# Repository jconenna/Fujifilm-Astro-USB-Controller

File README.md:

# Fujifilm-Astro-USB-Controller

USB Serial shutter release device for Fujifilm cameras, geared towards **Astrophotography** use.

## Description

This device was made in response to a lack of tethering options for Fujifilm cameras for **Astrophotography control**, though it can be used for general shutter release needs with manual lenses or lenses with autofocus disabled.</br>

This device allows a compatible Fujifilm camera to be controlled by [digiCamControl](http://digicamcontrol.com/) software (free, MS Windows) with its "Astro" intervalometer mode, which interoperates with [PHD2](https://openphdguiding.org/) software, allowing for autoguiding a mount and dithering between frames.</br>

The device was made using common, inexpensive, and easy to assemble parts that can be sourced from places like Amazon, Ebay, Sparkfun, and other retailers.</br>

An optoisolator isolates the 5V computer side circuit from the shutter release camera side of the circuit, providing some added safety.</br>

This has been tested working with an X-T100 and X-S10, and should work with other similarly controlled Fujifilm cameras (e.g. X-T#, X-T##, X-E#, X-T###, X###C, etc.) If you try this and it works for your camera let me know so I can build a compatibility list.</br>

This device has been tested working with some Canon cameras that use the 3 pin shutter release, though I am marketing this for Fujifilm folks since there is no BackyardFuji or other tethering option for most cameras.</br>

For astrophotography use with digiCamControl software, it has been tested working with an X-T100, camera lens, and Star Adventurer mount guided with PHD2 using an ASI120MM-Mini guide cam and 30mm guide scope, dithering between frames.</br>

You **may** be able to use this device with other camera control software that has a "Serial Shutter Release" option that uses the RTS signal as the signal to the device. </br>

## Theory of Operation
This device works by using software on a computer to control the RTS signal of an RS-232 connection (USB to Serial Converter in this case). The RTS signal from the Converter used here is inverted using a transistor since it comes from the FTDI chip inverted (cannot change EEPROM setting of **this** converter). When the signal reaching the optoisolator is asserted it turns on the internal IR LED whose photons turn on the internal IR Photodiode on the shutter release side, connecting the Shutter/Focus pins to the Ground pin of the shutter release cable, thereby closing the camera shutter.</br>

From inspection of commercial shutter release products for Fujifilm cameras, it was found that a successful shutter release depends on activating the focus pin before the shutter pin. For astrophotography a telescope or manually focused lens is typically used, thus the focus activation has no ill effect on composition. This device simultaneously activates the focus and shutter pins, successfully closing the shutter on the camera.</br> 

## What's Included
Included are the Eagle PCB files for ordering a board. Boards can be easily [purchased from OSH Park](https://oshpark.com/shared_projects/9drAsv7N) for around $11 for 3 boards. If you choose to order elsewhere, the 3D files are designed for a PCB thickness of 1.5-1.6mm. Note: I have no affiliation with OSH Park, but love their services.

Included are two stl files for 3D printing a case. This contains a top and bottom piece that snap together and can be easily printed without supports by a wide variety of printers. I used PLA material with default print settings on an Ender 3 Pro printer. 

## Bill of Materials:
1 - FT232RL USB to TTL Serial Converter module (red PCB with Mini USB female connector)<br/>
1 - PJ-307 3.5 mm Audio Jack Connector PCB Mount Female Socket 5 Pin<br/>
1 - 4N25 Optoisolator (6 pin DIP, white)<br/>
1 - 2N2222 NPN Transistor (TO-92 package)<br/>
2 - 1 kOhm Axial Resistor (common through hole resistor)<br/>
1 - 50 Ohm Axial Resistor (common through hole resistor)<br/>

## In addition you will need:
1 - A-Male to Mini-B USB Cable, length of your choice<br/>
1 - 3.5mm Audio Cable, length of your choice<br/>
1 - 3.5mm Female to 2.5mm Male adapter, preferably the short cable type with right angle 2.5mm connector<br/>
OR instead of the 2 previous items 1 - 3.5mm male to 2.5mm male Audio cable<br/>

## Tutorial

#### Assembly

[Here is a video showing from start to finish how I solder the components to the board.](https://youtu.be/rFp3plmKMuA)

#### Use with digiCamControl

1. [Download FTDI drivers here](https://cdn.sparkfun.com/assets/learn_tutorials/7/4/CDM21228_Setup.exe), or visit [FTDI's VCP Drivers page](https://ftdichip.com/drivers/) for the latest download of the Windows FTDI Driver executable.
2. Install the drivers using the executable file.
3. Open Windows Device Manager (Win-R, devmgmt.msc, OK).
4. Plug in the Fujifilm-Astro-USB-Controller device using the USB Mini cable.
5. Click the drop-down arrow for **Ports** and note "USB Serial Port" device. Right-click, properties, and note Manufacturer: FTDI. 
6. Note the COM number assigned to the device, in this case COM7.</br>

7. Download the latest stable version of [digiCamControl](http://digicamcontrol.com/download) and install.
8. Open digiCamControl.
9. Go to File > Settings.
10. In the popup window click on Devices, under available devices click Add.
11. Name the device under Configuration, set the driver as **Serial Port Shutter Release**, and Com Port to the COM port of the device.</br>

12. Click Ok in the bottom left of the Settings window to exit.
13. On the top toolbar click on the Astronomy button.</br>

14. In the popup BULB window, under the **External shutter release** menu, select enable and chose the device you just set up.</br>

15. Set the imaging session parameters:</br>

16. Set **Capture time** value in seconds.
17. Set **Number of photos** to set how many frames to capture before stopping.
18. Set **Time between shots** value in seconds. For non guided imaging I usually set this between 1-5.
19. If guiding with PHD2: open, setup, and begin guiding with PHD2. **If not guiding skip to Step 22.**
- Set **PHD Guiding** from (None) to Move1 - Move5 (Dither a random amount, up to +/- [0.5, 1.0, 2.0, 3.0, 5.0] x dither scale)
20. Set **Wait for PHD** to 20 seconds if dithering. This value will depend on how long it takes to from shutter closing to guiding being stable after a dither. For me 20 seconds was sufficient, but you may test to get a feel for this value. You could also set this value to 0 and set **Time between shots** to the necessary amount of time. If not dithering, then you can keep this at 0.</br>
21. It is not necessary in my experience to check the "Automatically PHD..." box.
22. Connect the shutter release cable from the Camera to the Fujifilm-Astro-USB-Controller device.
23. Turn on your device, set ISO, and put it in BULB mode. If camera is asleep, wake up with half shutter press.
24. To begin imaging press **Start Capture**.
25. If nothing happens and the BULB window shows "Error Shutter Access to the port is denied", turn off the camera, unplug and replug the Fujifilm-Astro-USB-Controller device, turn on the camera, press **Start Capture** again and it should work.

Some notes:</br>
If the camera falls asleep before you start imaging you will have to wake it up with a button press before pressing **Start Capture**.

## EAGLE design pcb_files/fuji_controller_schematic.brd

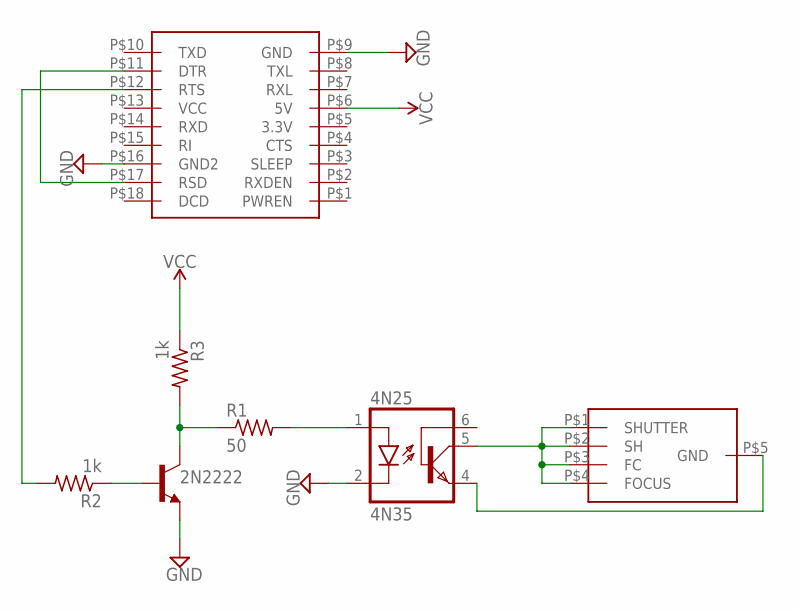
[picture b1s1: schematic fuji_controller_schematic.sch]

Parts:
2N2222: -NPN-TO92-EBC; TO92-EBC
3.5MM: 3.5MM_AUDIO_JACK
4N25: 4N35; DIL06
FTDI: FTDI_BREAKOUT; FTDI232_BREAKOUT
R1: 50; 0204/7
R2, R3: 1k; 0204/7

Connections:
GND: 2N2222.E, 4N25.2 (C), FTDI.P$9 (GND), FTDI.P$16 (GND2)
unnamed: FTDI.P$11 (DTR), FTDI.P$17 (RSD)
unnamed: FTDI.P$12 (RTS), R2.2
unnamed: 2N2222.B, R2.1
unnamed: 2N2222.C, R1.1, R3.2
unnamed: 4N25.1 (A), R1.2
unnamed: 3.5MM.P$1 (SHUTTER), 3.5MM.P$2 (SH), 3.5MM.P$3 (FC), 3.5MM.P$4 (FOCUS), 4N25.5 (COL)
unnamed: 3.5MM.P$5 (GND), 4N25.4 (EMI)
VCC: FTDI.P$6 (5V), R3.1

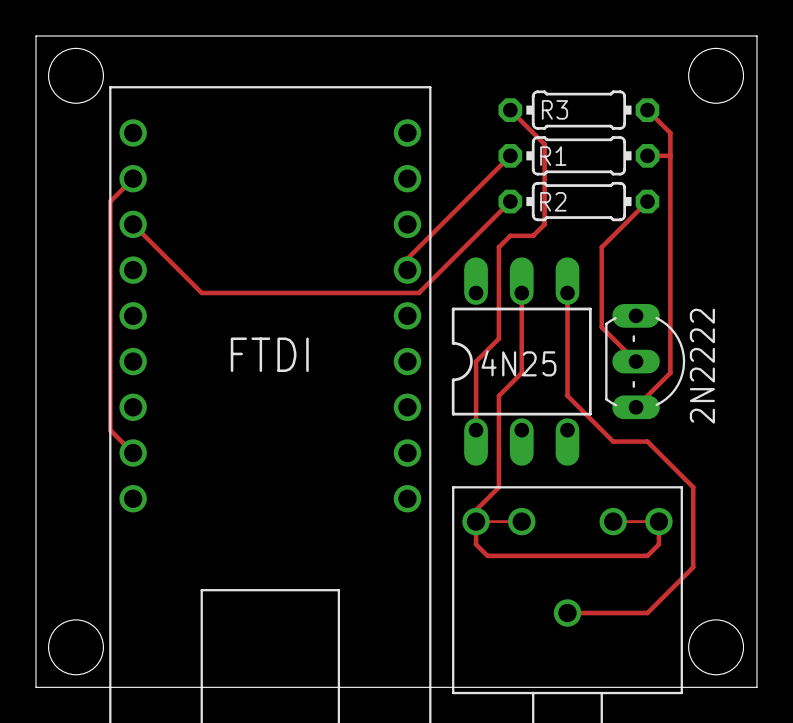
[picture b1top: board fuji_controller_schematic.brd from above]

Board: 2 copper layers, 40.1 x 36.2 mm, 7 parts (0 on the bottom side), 9 nets.

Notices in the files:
parts and their libraries:
SparkFun-PowerSymbols: Licensing: Creative Commons ShareAlike 4.0 International - https://creativecommons.org/licenses/by-sa/4.0
